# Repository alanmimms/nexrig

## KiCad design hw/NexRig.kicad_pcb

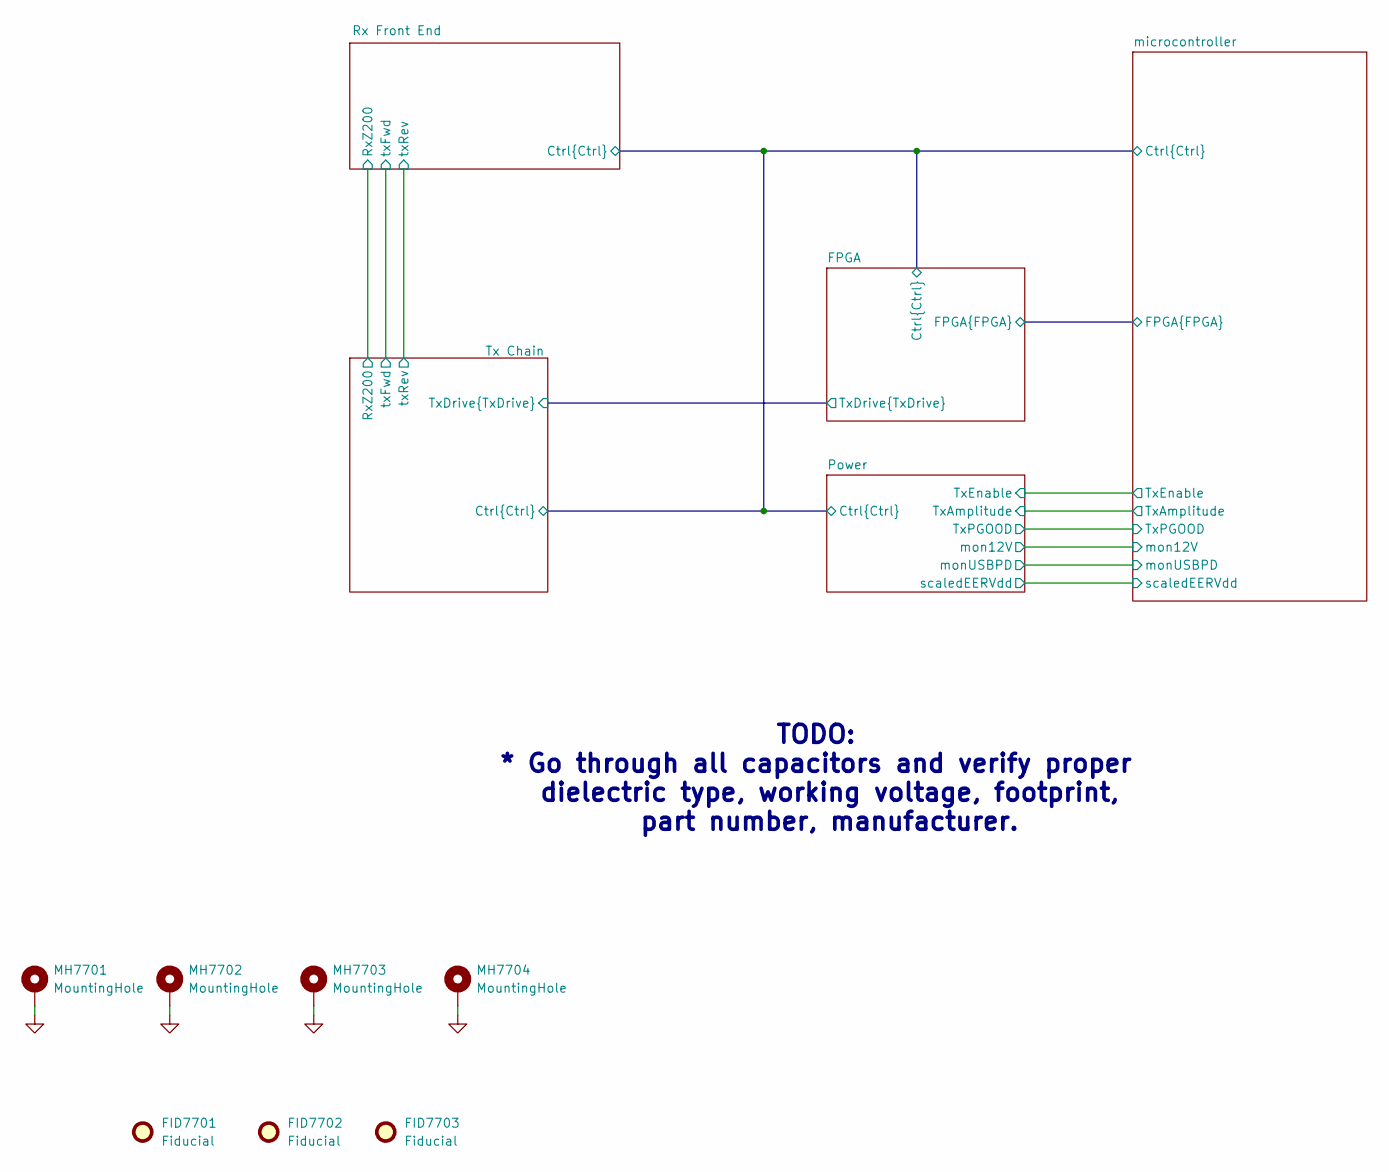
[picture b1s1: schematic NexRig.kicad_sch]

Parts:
FID7701, FID7702, FID7703: Fiducial; Fiducial_0.5mm_Mask2mm
MH7701, MH7702, MH7703, MH7704: MountingHole; MountingHole_3.2mm_M3_ISO7380_Pad

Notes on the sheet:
TODO: * Go through all capacitors and verify proper dielectric type, working voltage, footprint, part number, manufacturer.

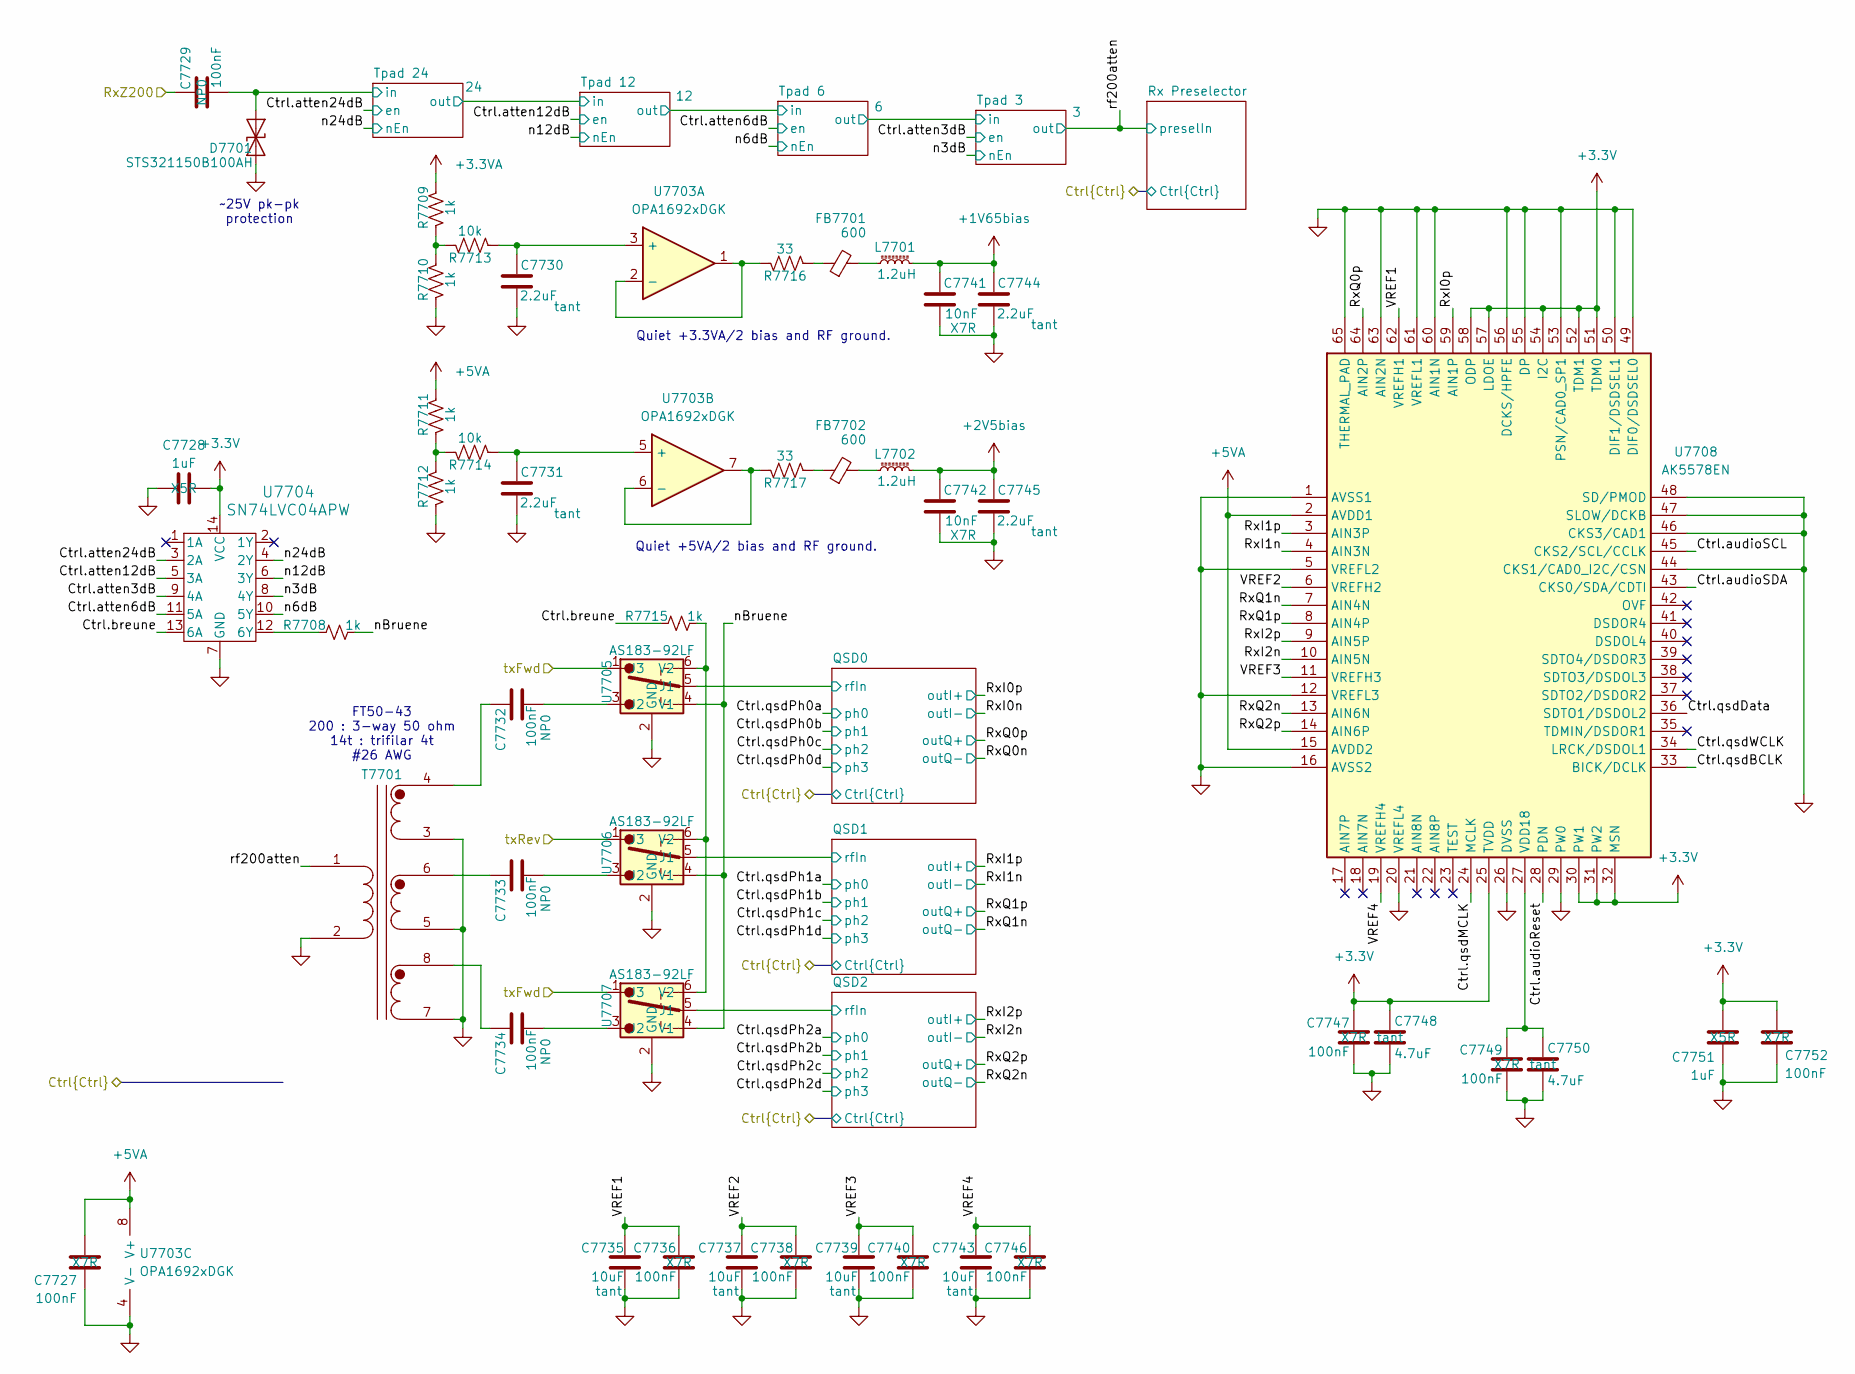
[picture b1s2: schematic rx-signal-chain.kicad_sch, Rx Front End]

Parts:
C7727, C7736, C7738, C7740, C7746, C7747, C7749, C7752: 100nF; C_0603_1608Metric; Manufacturer_Part_Number C0805F104K1RACAUTO; Mouser Part Number 80-C0805F104K1RAUTO
C7728, C7751: 1uF; C_0402_1005Metric; Manufacturer_Part_Number GRM155R61E105KE11D; Mouser Part Number 81-GRM155R61E105KE1D
C7729, C7732, C7733, C7734: 100nF; C_1206_3216Metric; Manufacturer_Part_Number GRM31C5C2A104JA01L; Mouser Part Number 81-GRM31C5C2A104JA1L
C7730, C7731, C7744, C7745: 2.2uF; C_0805_2012Metric; MfgPart T55B225M050C0200; Mouser Part Number 74-TMCP1D225MTR2F
C7735, C7737, C7739, C7743: 10uF; C_0805_2012Metric; MfgPart TMCP0J106KTR2F; Mouser Part Number 581-TAJD106K050R
C7741, C7742: 10nF; C_0603_1608Metric; Part Number GCM1885C2A103JE02J; Mouser Part Number 81-GCM1885C2A103JE2J
C7748, C7750: 4.7uF; C_0805_2012Metric; Manufacturer_Part_Number 298D475X9010M2T; Mouser Part Number 74-298D475X9010M2T
D7701: STS321150B100AH; Infineon_SG-WLL-2-3_0.58x0.28_P0.36mm
FB7701, FB7702: 600; L_0603_1608Metric; MfgPN BLM18AG601SN1D
L7701, L7702: 1.2uH; L_0805_2012Metric; Part Number CWF2012A-1R2K
R7708, R7715: 1k; R_0402_1005Metric
R7709, R7710, R7711, R7712: 1k; R_0603_1608Metric
R7713, R7714: 10k; R_0402_1005Metric
R7716, R7717: 33; R_0603_1608Metric
T7701: 12t primary : 6T #26 trifilar secondary FT37-43; Toroid-1pri-3sec-ft50
U7703: OPA1692xDGK; VSSOP-8_3x3mm_P0.65mm
U7704: SN74LVC04APW; PW14
U7705, U7706, U7707: AS183-92LF; SOT65P220X110-6N; Mouser Part Number 873-AS183-92LF
U7708: AK5578EN; QFN50P900X900X100-65N; Mouser Part Number 412-AK5578EN

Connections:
+1V65bias: C7741.1, C7744.1, L7701.2; also elsewhere on the board
+2V5bias: C7742.1, C7745.1, L7702.2; also elsewhere on the board
+3.3V: C7728.2, C7747.2, C7748.2, C7751.1, C7752.1, U7704.14 (VCC), U7708.25 (TVDD), U7708.30 (PW1), U7708.31 (PW2), U7708.32 (MSN), U7708.51 (TDM0), U7708.52 (TDM1), U7708.54 (I2C), U7708.57 (LDOE), U7708.58 (ODP); also elsewhere on the board
+3.3VA: R7709.2; also elsewhere on the board
+5VA: C7727.1, R7711.2, U7703.8 (V+), U7708.2 (AVDD1), U7708.15 (AVDD2); also elsewhere on the board
/FPGA/Ctrl.audioReset: U7708.28 (PDN); also elsewhere on the board
/FPGA/Ctrl.audioSCL: U7708.45 (CKS2/SCL/CCLK); also elsewhere on the board
/FPGA/Ctrl.audioSDA: U7708.43 (CKS0/SDA/CDTI); also elsewhere on the board
/FPGA/Ctrl.qsdBCLK: U7708.33 (BICK/DCLK); also elsewhere on the board
/FPGA/Ctrl.qsdData: U7708.36 (SDTO1/DSDOL2); also elsewhere on the board
/FPGA/Ctrl.qsdMCLK: U7708.24 (MCLK)
/FPGA/Ctrl.qsdWCLK: U7708.34 (LRCK/DSDOL1); also elsewhere on the board
/Rx Front End/Ctrl.atten3dB: U7704.9 (4A); also elsewhere on the board
/Rx Front End/Ctrl.atten6dB: U7704.11 (5A); also elsewhere on the board
/Rx Front End/Ctrl.atten12dB: U7704.5 (3A); also elsewhere on the board
/Rx Front End/Ctrl.atten24dB: U7704.3 (2A); also elsewhere on the board
/Rx Front End/Ctrl.breune: R7715.1, U7704.13 (6A)
/Rx Front End/QSD0/rfIn: U7705.5 (J1); also elsewhere on the board
/Rx Front End/QSD1/rfIn: U7706.5 (J1); also elsewhere on the board
/Rx Front End/QSD2/rfIn: U7707.5 (J1); also elsewhere on the board
/Rx Front End/RxI0p: U7708.59 (AIN1P); also elsewhere on the board
/Rx Front End/RxI1n: U7708.4 (AIN3N); also elsewhere on the board
/Rx Front End/RxI1p: U7708.3 (AIN3P); also elsewhere on the board
/Rx Front End/RxI2n: U7708.10 (AIN5N); also elsewhere on the board
/Rx Front End/RxI2p: U7708.9 (AIN5P); also elsewhere on the board
/Rx Front End/RxQ0p: U7708.64 (AIN2P); also elsewhere on the board
/Rx Front End/RxQ1n: U7708.7 (AIN4N); also elsewhere on the board
/Rx Front End/RxQ1p: U7708.8 (AIN4P); also elsewhere on the board
/Rx Front End/RxQ2n: U7708.13 (AIN6N); also elsewhere on the board
/Rx Front End/RxQ2p: U7708.14 (AIN6P); also elsewhere on the board
/Rx Front End/RxZ200: C7729.1; also elsewhere on the board
/Rx Front End/Tpad 24/in: C7729.2, D7701.1 (A1); also elsewhere on the board
/Rx Front End/VREF1: C7735.1, C7736.1, U7708.62 (VREFH1)
/Rx Front End/VREF2: C7737.1, C7738.1, U7708.6 (VREFH2)
/Rx Front End/VREF3: C7739.1, C7740.1, U7708.11 (VREFH3)
/Rx Front End/VREF4: C7743.1, C7746.1, U7708.19 (VREFH4)
/Rx Front End/n3dB: U7704.8 (4Y); also elsewhere on the board
/Rx Front End/n6dB: U7704.10 (5Y); also elsewhere on the board
/Rx Front End/n12dB: U7704.6 (3Y); also elsewhere on the board
/Rx Front End/n24dB: U7704.4 (2Y); also elsewhere on the board
/Rx Front End/nBruene: R7708.2, U7705.4 (V1), U7706.4 (V1), U7707.4 (V1)
/Rx Front End/rf200atten: T7701.1 (IN+); also elsewhere on the board
/Rx Front End/txFwd: U7705.1 (J3), U7707.1 (J3); also elsewhere on the board
/Rx Front End/txRev: U7706.1 (J3); also elsewhere on the board
unnamed: C7733.1, T7701.6 (OUT2A)
unnamed: C7734.1, T7701.8 (OUT2A)
unnamed: FB7701.1, R7716.1
unnamed: FB7701.2, L7701.1
unnamed: FB7702.1, R7717.1
unnamed: FB7702.2, L7702.1
unnamed: R7709.1, R7710.2, R7713.2
unnamed: R7711.1, R7712.2, R7714.2
unnamed: C7732.1, T7701.4 (OUT1A)
unnamed: C7730.1, R7713.1, U7703.3 (+)
unnamed: R7716.2, U7703.1, U7703.2 (-)
unnamed: C7731.1, R7714.1, U7703.5 (+)
unnamed: R7717.2, U7703.6 (-), U7703.7
unnamed: R7708.1, U7704.12 (6Y)
unnamed: C7732.2, U7705.3 (J2)
unnamed: R7715.2, U7705.6 (V2), U7706.6 (V2), U7707.6 (V2)
unnamed: C7733.2, U7706.3 (J2)
unnamed: C7734.2, U7707.3 (J2)
unnamed: C7749.2, C7750.2, U7708.27 (VDD18)

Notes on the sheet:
~25V pk-pk protection
Quiet +3.3VA/2 bias and RF ground.
FT50-43 200 : 3-way 50 ohm 14t : trifilar 4t #26 AWG
Quiet +5VA/2 bias and RF ground.

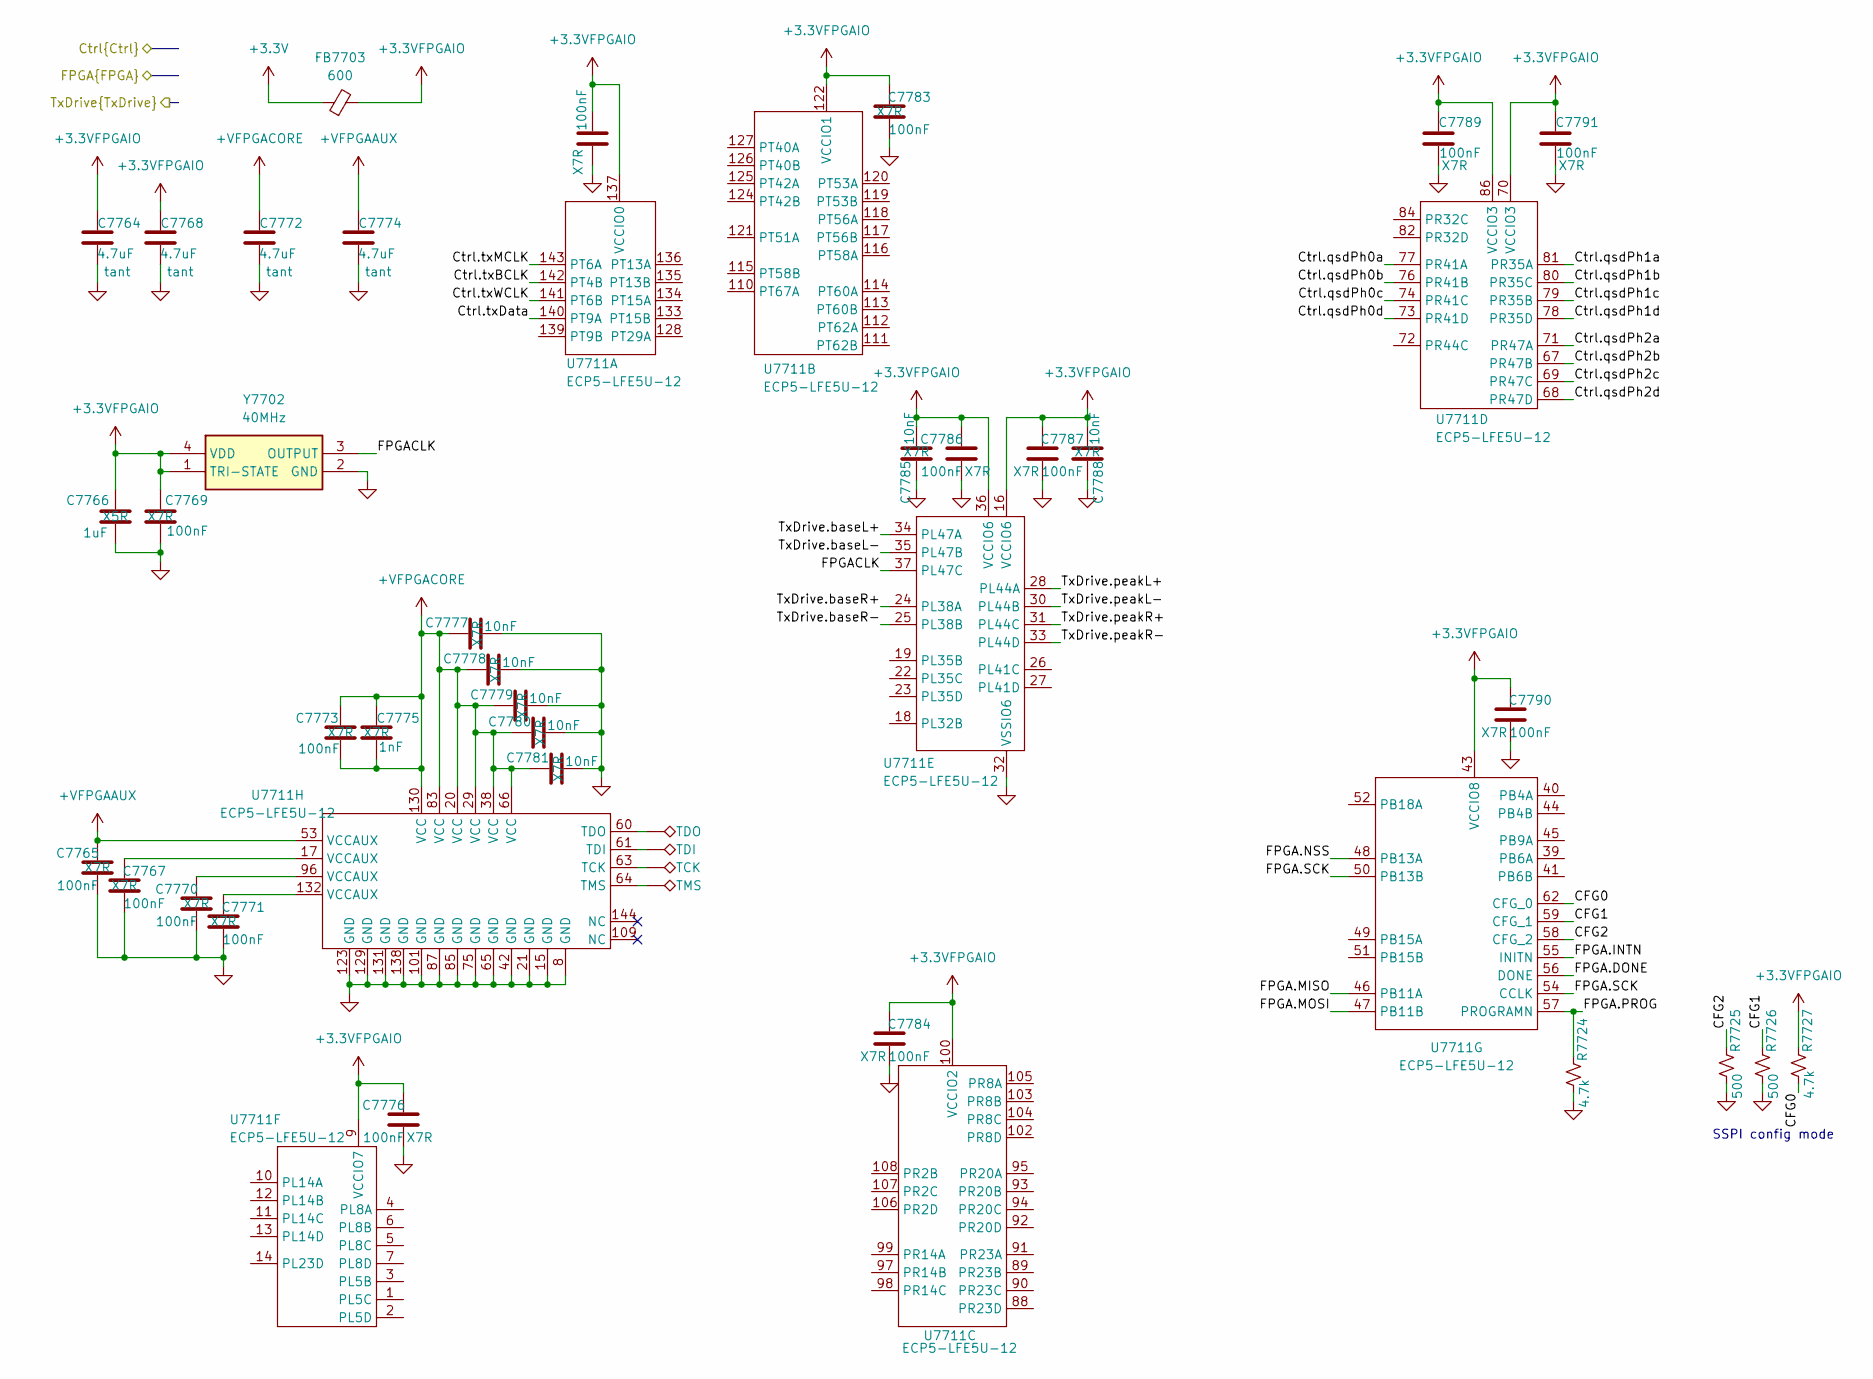
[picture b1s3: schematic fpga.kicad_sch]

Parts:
C7764, C7768, C7772, C7774: 4.7uF; C_0805_2012Metric; Manufacturer_Part_Number 298D475X9010M2T; Mouser Part Number 74-298D475X9010M2T
C7765, C7767, C7769, C7770, C7771, C7773, C7776, C7782, C7783, C7784, C7786, C7787, C7789, C7790, C7791: 100nF; C_0603_1608Metric; Manufacturer_Part_Number C0805F104K1RACAUTO; Mouser Part Number 80-C0805F104K1RAUTO
C7766: 1uF; C_0402_1005Metric; Manufacturer_Part_Number GRM155R61E105KE11D; Mouser Part Number 81-GRM155R61E105KE1D
C7775: 1nF; C_0603_1608Metric; Manufacturer_Part_Number KAF15AR71H102KM; Mouser Part Number 581-KAF15AR71H102KM
C7777, C7778, C7779, C7780, C7781, C7785, C7788: 10nF; C_0603_1608Metric; Manufacturer_Part_Number GCM1885C2A103JE02J; Mouser Part Number 81-GCM1885C2A103JE2J
FB7703: 600; L_0603_1608Metric
PG7709: TDO; TestPoint_Pad_1.0x1.0mm
PG7710: TDI; TestPoint_Pad_1.0x1.0mm
PG7711: TCK; TestPoint_Pad_1.0x1.0mm
PG7712: TMS; TestPoint_Pad_1.0x1.0mm
R7724, R7727: 4.7k; R_0603_1608Metric
R7725, R7726: 500; R_0603_1608Metric
U7711: ECP5-LFE5U-12; TQFP-144_20x20mm_P0.5mm
Y7702: 40MHz; ECSTXO201633400TR; Mouser Part Number 520-TXO-2016-33-400T

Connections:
+3.3V: FB7703.1; also elsewhere on the board
+3.3VFPGAIO: C7764.1, C7766.1, C7768.1, C7769.1, C7776.1, C7782.1, C7783.1, C7784.1, C7785.1, C7786.1, C7787.1, C7788.1, C7789.1, C7790.1, C7791.1, FB7703.2, R7727.1, U7711.9 (VCCIO7), U7711.16 (VCCIO6), U7711.36 (VCCIO6), U7711.43 (VCCIO8), U7711.70 (VCCIO3), U7711.86 (VCCIO3), U7711.100 (VCCIO2), U7711.122 (VCCIO1), U7711.137 (VCCIO0), Y7702.1 (TRI-STATE), Y7702.4 (VDD)
+VFPGAAUX: C7765.1, C7774.1, U7711.53 (VCCAUX); also elsewhere on the board
+VFPGACORE: C7772.1, C7773.1, C7773.2, C7775.1, C7775.2, C7777.2, C7778.2, C7779.2, C7780.2, C7781.2, U7711.20 (VCC), U7711.29 (VCC), U7711.38 (VCC), U7711.66 (VCC), U7711.83 (VCC), U7711.130 (VCC); also elsewhere on the board
/FPGA/CFG0: R7727.2, U7711.62 (CFG_0)
/FPGA/CFG1: R7726.1, U7711.59 (CFG_1)
/FPGA/CFG2: R7725.1, U7711.58 (CFG_2)
/FPGA/Ctrl.qsdPh0a: U7711.77 (PR41A); also elsewhere on the board
/FPGA/Ctrl.qsdPh0b: U7711.76 (PR41B); also elsewhere on the board
/FPGA/Ctrl.qsdPh0c: U7711.74 (PR41C); also elsewhere on the board
/FPGA/Ctrl.qsdPh0d: U7711.73 (PR41D); also elsewhere on the board
/FPGA/Ctrl.qsdPh1a: U7711.81 (PR35A); also elsewhere on the board
/FPGA/Ctrl.qsdPh1b: U7711.80 (PR35C); also elsewhere on the board
/FPGA/Ctrl.qsdPh1c: U7711.79 (PR35B); also elsewhere on the board
/FPGA/Ctrl.qsdPh1d: U7711.78 (PR35D); also elsewhere on the board
/FPGA/Ctrl.qsdPh2a: U7711.71 (PR47A); also elsewhere on the board
/FPGA/Ctrl.qsdPh2b: U7711.67 (PR47B); also elsewhere on the board
/FPGA/Ctrl.qsdPh2c: U7711.69 (PR47C); also elsewhere on the board
/FPGA/Ctrl.qsdPh2d: U7711.68 (PR47D); also elsewhere on the board
/FPGA/Ctrl.txBCLK: U7711.142 (PT4B); also elsewhere on the board
/FPGA/Ctrl.txData: U7711.140 (PT9A); also elsewhere on the board
/FPGA/Ctrl.txMCLK: U7711.143 (PT6A); also elsewhere on the board
/FPGA/Ctrl.txWCLK: U7711.141 (PT6B); also elsewhere on the board
/FPGA/FPGA.DONE: U7711.56 (DONE); also elsewhere on the board
/FPGA/FPGA.INTN: U7711.55 (INITN); also elsewhere on the board
/FPGA/FPGA.MISO: U7711.46 (PB11A); also elsewhere on the board
/FPGA/FPGA.MOSI: U7711.47 (PB11B); also elsewhere on the board
/FPGA/FPGA.NSS: U7711.48 (PB13A); also elsewhere on the board
/FPGA/FPGA.PROG: R7724.1, U7711.57 (PROGRAMN); also elsewhere on the board
/FPGA/FPGA.SCK: U7711.50 (PB13B), U7711.54 (CCLK); also elsewhere on the board
/FPGA/FPGACLK: U7711.37 (PL47C), Y7702.3 (OUTPUT)
/FPGA/TxDrive.baseL+: U7711.34 (PL47A); also elsewhere on the board
/FPGA/TxDrive.baseL-: U7711.35 (PL47B); also elsewhere on the board
/FPGA/TxDrive.baseR+: U7711.24 (PL38A); also elsewhere on the board
/FPGA/TxDrive.baseR-: U7711.25 (PL38B); also elsewhere on the board
/FPGA/TxDrive.peakL+: U7711.28 (PL44A); also elsewhere on the board
/FPGA/TxDrive.peakL-: U7711.30 (PL44B); also elsewhere on the board
/FPGA/TxDrive.peakR+: U7711.31 (PL44C); also elsewhere on the board
/FPGA/TxDrive.peakR-: U7711.33 (PL44D); also elsewhere on the board
unnamed: C7767.1, U7711.17 (VCCAUX)
unnamed: C7770.1, U7711.96 (VCCAUX)
unnamed: C7771.1, U7711.132 (VCCAUX)
unnamed: PG7711.1, U7711.63 (TCK)
unnamed: PG7710.1, U7711.61 (TDI)
unnamed: PG7709.1, U7711.60 (TDO)
unnamed: PG7712.1, U7711.64 (TMS)

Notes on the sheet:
SSPI config mode

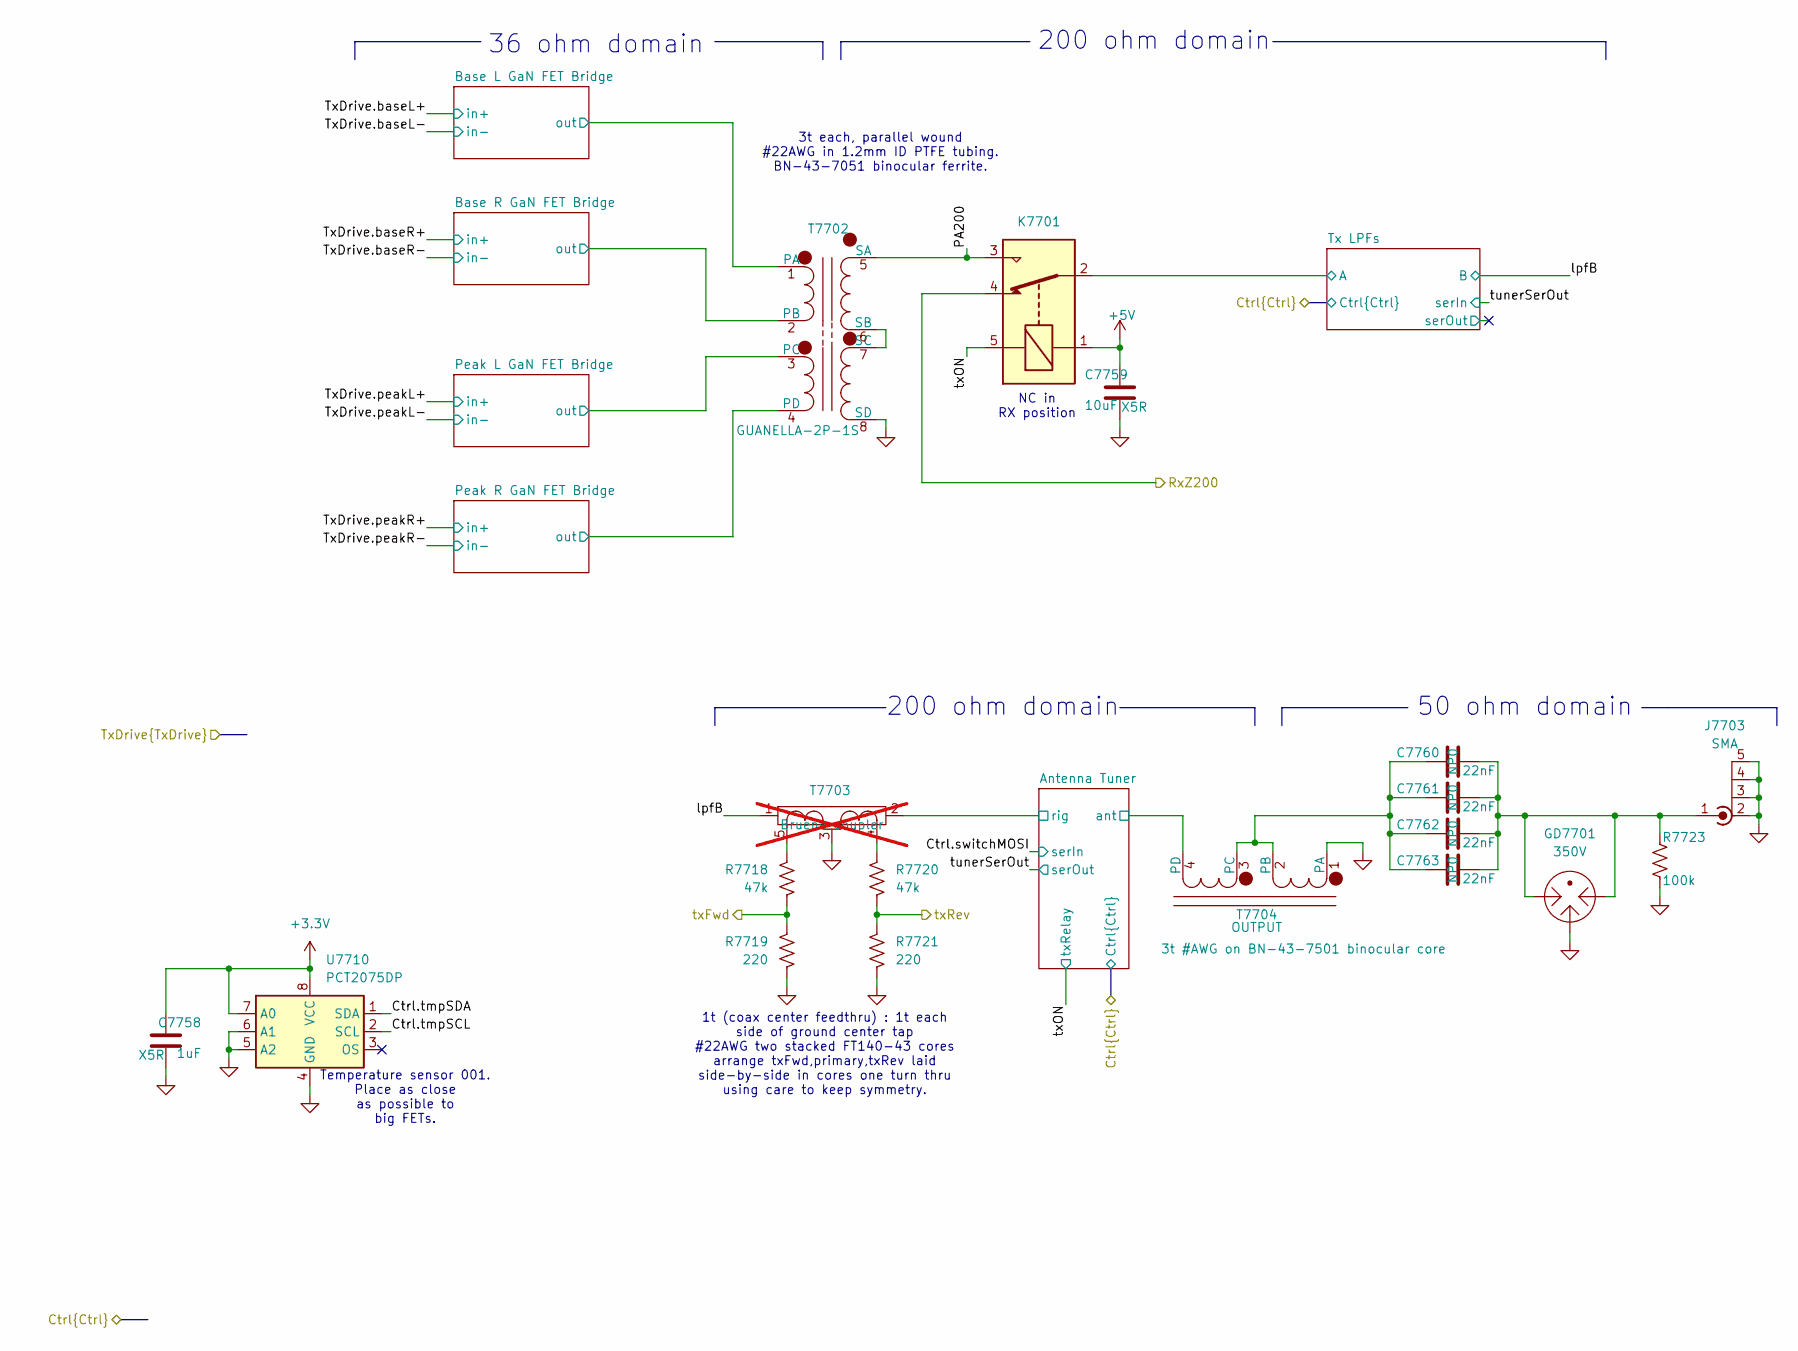
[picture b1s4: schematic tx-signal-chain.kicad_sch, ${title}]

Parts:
C7758: 1uF; C_0402_1005Metric; Manufacturer_Part_Number GRM155R61E105KE11D; Mouser Part Number 81-GRM155R61E105KE1D
C7759: 10uF; C_0603_1608Metric; Manufacturer_Part_Number 81-GXT155R71E223KE1D; Mouser Part Number 963-MLAST168BB5106MT
C7760, C7761, C7762, C7763: 22nF; C_1206_3216Metric; Manufacturer_Part_Number CC1210JKNPOCBN223; Mouser Part Number 603-CC121JKNPOCBN223
GD7701: 350V; GDT3535S1RP; Manufacturer_Part_Number GDT35-35-S1-RP; Mouser Part Number 652-GDT35-35-S1-RP
J7703: SMA; RFPCSMA27F
K7701: G5Q-14-05; Relay_SPDT_Omron-G5Q-1
R7718, R7720: 47k; R_0603_1608Metric; Manufacturer_Part_Number MCT06030C4702FP500; Mouser Part Number 594-MCT06030C4702FP5
R7719, R7721: 220; R_0603_1608Metric; Manufacturer_Part_Number MCT06030C2200FP500; Mouser Part Number 594-MCT06030C2200FP5
R7723: 100k; R_1206_3216Metric; Manufacturer_Part_Number ERJ-P08J104V; Mouser Part Number 667-ERJ-P08J104V
T7702: GUANELLA-2P-1S; Guanella-2P-2S
T7703: Bruene coupler; BN-43-7051-1P-1S-CT; not fitted
T7704: OUTPUT; Guanella-1P-1S
U7710: PCT2075DP; TSSOP-8_3x3mm_P0.65mm

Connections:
+3.3V: C7758.1, U7710.7 (A0), U7710.8 (VCC); also elsewhere on the board
/FPGA/Ctrl.tmpSCL: U7710.2 (SCL); also elsewhere on the board
/FPGA/Ctrl.tmpSDA: U7710.1 (SDA); also elsewhere on the board
/Rx Front End/txFwd: R7718.2, R7719.1; also elsewhere on the board
/Rx Front End/txRev: R7720.2, R7721.1; also elsewhere on the board
/Tx Chain/Antenna Tuner/rig: T7703.2; also elsewhere on the board
/Tx Chain/Base L GaN FET Bridge/out: T7702.1 (PA); also elsewhere on the board
/Tx Chain/Base R GaN FET Bridge/out: T7702.2 (PB); also elsewhere on the board
/Tx Chain/Peak L GaN FET Bridge/out: T7702.3 (PC); also elsewhere on the board
/Tx Chain/Peak R GaN FET Bridge/out: T7702.4 (PD); also elsewhere on the board
/Tx Chain/lpfB: T7703.1; also elsewhere on the board
/Tx Chain/txON: K7701.5; also elsewhere on the board
unnamed: C7760.2, C7761.2, C7762.2, C7763.2, GD7701.1, GD7701.3, J7703.1 (In), R7723.1
unnamed 312: K7701.4; also elsewhere on the board
unnamed: R7718.1, T7703.5
unnamed: R7720.1, T7703.4
unnamed: T7702.6 (SB), T7702.7 (SC)
unnamed: C7760.1, C7761.1, C7762.1, C7763.1, T7704.2 (PB), T7704.3 (PC)

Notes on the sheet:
50 ohm domain
1t (coax center feedthru) : 1t each side of ground center tap #22AWG two stacked FT140-43 cores arrange txFwd,primary,txRev laid side-by-side in cores one turn thru using care to keep symmetry.
3t each, parallel wound #22AWG in 1.2mm ID PTFE tubing. BN-43-7051 binocular ferrite.
36 ohm domain
200 ohm domain
NC in RX position
Temperature sensor 001. Place as close as possible to big FETs.

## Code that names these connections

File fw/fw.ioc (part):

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Mcu.Name=STM32H753ZITx
Mcu.Package=LQFP144
Mcu.UserName=STM32H753ZITx
PA1.GPIOParameters=GPIO_Label
PA1.GPIO_Label=EthCLK
PA1.Mode=RMII
PA1.Signal=ETH_REF_CLK
PA11.GPIOParameters=GPIO_PuPd,GPIO_Label
PA11.GPIO_Label=TxEnable
PA11.GPIO_PuPd=GPIO_PULLDOWN
PA11.Signal=GPIO_Output
PA13\ (JTMS/SWDIO).GPIOParameters=GPIO_Label
PA13\ (JTMS/SWDIO).GPIO_Label=SWDIO
PA13\ (JTMS/SWDIO).Mode=Serial_Wire
PA13\ (JTMS/SWDIO).Signal=DEBUG_JTMS-SWDIO
PA14\ (JTCK/SWCLK).GPIOParameters=GPIO_Label
PA14\ (JTCK/SWCLK).GPIO_Label=SWCL
PA14\ (JTCK/SWCLK).Mode=Serial_Wire
PA14\ (JTCK/SWCLK).Signal=DEBUG_JTCK-SWCLK
PA15\ (JTDI).GPIOParameters=GPIO_Speed,GPIO_PuPd,GPIO_Label
PA15\ (JTDI).GPIO_Label=FPGA_NSS
PA15\ (JTDI).GPIO_PuPd=GPIO_PULLUP
PA15\ (JTDI).GPIO_Speed=GPIO_SPEED_FREQ_MEDIUM
PA15\ (JTDI).Mode=NSS_Signal_Hard_Output
PA15\ (JTDI).Signal=SPI3_NSS
PA2.GPIOParameters=GPIO_Label
PA2.GPIO_Label=EthMDIO
PA2.Mode=RMII
PA2.Signal=ETH_MDIO
PA4.GPIOParameters=GPIO_Label
PA4.GPIO_Label=TxAmplitude
PA4.Signal=COMP_DAC11_group
PA5.GPIOParameters=GPIO_Label
PA5.GPIO_Label=Ctrl.tuneSCK
PA5.Mode=TX_Only_Simplex_Unidirect_Master
PA5.Signal=SPI6_SCK
PA6.GPIOParameters=GPIO_PuPd,GPIO_Label
PA6.GPIO_Label=Ctrl_audioReset
PA6.GPIO_PuPd=GPIO_PULLDOWN
PA6.Signal=GPIO_Output
PA7.GPIOParameters=GPIO_Label
PA7.GPIO_Label=EthCRS_DV
PA7.Mode=RMII
PA7.Signal=ETH_CRS_DV
PA8.Signal=GPIO_Analog
PA9.GPIOParameters=GPIO_Label
PA9.GPIO_Label=monUSBPD
PA9.Signal=GPIO_Analog
PB10.GPIOParameters=GPIO_Speed,GPIO_Label
PB10.GPIO_Label=Ctrl_switchSCK
PB10.GPIO_Speed=GPIO_SPEED_FREQ_HIGH
PB10.Mode=TX_Only_Simplex_Unidirect_Master
PB10.Signal=SPI2_SCK
PB11.GPIOParameters=GPIO_Label
PB11.GPIO_Label=EthTxEnable
PB11.Mode=RMII
PB11.Signal=ETH_TX_EN
PB12.GPIOParameters=GPIO_Label
PB12.GPIO_Label=EthTXD0
PB12.Mode=RMII
PB12.Signal=ETH_TXD0
PB13.GPIOParameters=GPIO_Label
PB13.GPIO_Label=EthTXD1
PB13.Mode=RMII
PB13.Signal=ETH_TXD1
PB2.GPIOParameters=GPIO_Label
PB2.GPIO_Label=Ctrl.qsdData
PB2.Mode=SAI_A_AsyncSlave
PB2.Signal=SAI1_SD_A
PB3\ (JTDO/TRACESWO).Signal=DEBUG_JTDO-SWO
PB6.GPIOParameters=GPIO_Speed,GPIO_Label,GPIO_Pu
PB6.GPIO_Label=Ctrl_tmpSCL
PB6.GPIO_Pu=GPIO_PULLUP
PB6.GPIO_Speed=GPIO_SPEED_FREQ_MEDIUM
PB6.Mode=I2C
PB6.Signal=I2C1_SCL
PB7.GPIOParameters=GPIO_Speed,GPIO_Label,GPIO_Pu
PB7.GPIO_Label=Ctrl_tmpSDA
PB7.GPIO_Pu=GPIO_PULLUP
PB7.GPIO_Speed=GPIO_SPEED_FREQ_MEDIUM
PB7.Mode=I2C
PB7.Signal=I2C1_SDA
PC0.GPIOParameters=GPIO_Label
PC0.GPIO_Label=Ctrl_enable5V
PC0.Signal=GPIO_Output
PC1.GPIOParameters=GPIO_Label
PC1.GPIO_Label=EthMDC
PC1.Mode=RMII
PC1.Signal=ETH_MDC
PC10.GPIOParameters=GPIO_Speed,GPIO_Label
PC10.GPIO_Label=FPGA_SCK
PC10.GPIO_Speed=GPIO_SPEED_FREQ_HIGH
PC10.Mode=Full_Duplex_Master
PC10.Signal=SPI3_SCK
PC11.GPIOParameters=GPIO_PuPd,GPIO_Label
PC11.GPIO_Label=FPGA_MISO
PC11.GPIO_PuPd=GPIO_PULLUP
PC11.Mode=Full_Duplex_Master
PC11.Signal=SPI3_MISO
PC12.GPIOParameters=GPIO_Label,GPIO_Speed
PC12.GPIO_Label=FPGA_MOSI
PC12.GPIO_Speed=GPIO_SPEED_FREQ_HIGH
PC12.Mode=Full_Duplex_Master
PC12.Signal=SPI3_MOSI
PC3_C.GPIOParameters=GPIO_Speed,GPIO_Label
PC3_C.GPIO_Label=Ctrl_switchMOSI
PC3_C.GPIO_Speed=GPIO_SPEED_FREQ_HIGH
PC3_C.Mode=TX_Only_Simplex_Unidirect_Master
PC3_C.Signal=SPI2_MOSI
PC4.GPIOParameters=GPIO_Label
PC4.GPIO_Label=EthRXD0
PC4.Mode=RMII
PC4.Signal=ETH_RXD0
PC5.GPIOParameters=GPIO_Label
PC5.GPIO_Label=EthRXD1
PC5.Mode=RMII
PC5.Signal=ETH_RXD1
PC6.GPIOParameters=GPIO_PuPd,GPIO_Label
PC6.GPIO_Label=TxPGOOD
PC6.GPIO_PuPd=GPIO_PULLDOWN
PC6.Signal=GPIO_Input
PC8.GPIOParameters=GPIO_Label
PC8.GPIO_Label=Ctrl_bruene
PC8.Signal=GPIO_Output
PD12.GPIOParameters=GPIO_Speed,GPIO_Label,GPIO_Pu
PD12.GPIO_Label=Ctrl_audioSCL
PD12.GPIO_Pu=GPIO_NOPULL
PD12.GPIO_Speed=GPIO_SPEED_FREQ_MEDIUM
PD12.Mode=I2C
PD12.Signal=I2C4_SCL
PD7.GPIOParameters=GPIO_Speed,GPIO_Label
PD7.GPIO_Label=dispMOSI
PD7.GPIO_Speed=GPIO_SPEED_FREQ_HIGH
PD7.Mode=TX_Only_Simplex_Unidirect_Master
PD7.Signal=SPI1_MOSI
PE0.GPIOParameters=GPIO_PuPd,GPIO_Label
PE0.GPIO_Label=CDONE
PE0.GPIO_PuPd=GPIO_PULLDOWN
PE0.Signal=GPIO_Input
PE10.GPIOParameters=GPIO_Label
PE10.GPIO_Label=Ctrl_atten3dB
PE10.Signal=GPIO_Output
PE11.GPIOParameters=GPIO_PuPd,GPIO_Label
PE11.GPIO_Label=Ctrl.qsdNSS
PE11.GPIO_PuPd=GPIO_PULLUP
PE11.Mode=NSS_Signal_Hard_Output
PE11.Signal=SPI4_NSS
PE12.GPIOParameters=GPIO_PuPd,GPIO_Label
PE12.GPIO_Label=dispRESET
PE12.GPIO_PuPd=GPIO_PULLDOWN
PE12.Signal=GPIO_Output
PE13.GPIOParameters=GPIO_Label
PE13.GPIO_Label=dispDC
PE13.Signal=GPIO_Output
PE15.GPIOParameters=GPIO_PuPd,GPIO_Label
PE15.GPIO_Label=FPGA.RESET
PE15.GPIO_PuPd=GPIO_PULLDOWN
PE15.Signal=GPIO_Output
PE2.GPIOParameters=GPIO_Speed,GPIO_Label
PE2.GPIO_Label=Ctrl.qsdSCK
PE2.GPIO_Speed=GPIO_SPEED_FREQ_HIGH
PE2.Mode=TX_Only_Simplex_Unidirect_Master
PE2.Signal=SPI4_SCK
PE3.GPIOParameters=GPIO_Label
PE3.GPIO_Label=Ctrl.txData
PE3.Mode=SAI_B_MasterWithClock
PE3.Signal=SAI1_SD_B
PE4.GPIOParameters=GPIO_Label
PE4.GPIO_Label=Ctrl.qsdWCLK
PE4.Mode=SAI_A_AsyncSlave
PE4.Signal=SAI1_FS_A
PE5.GPIOParameters=GPIO_Label
PE5.GPIO_Label=Ctrl.qsdBCLK
PE5.Mode=SAI_A_AsyncSlave
PE5.Signal=SAI1_SCK_A
PE6.GPIOParameters=GPIO_Label
PE6.GPIO_Label=Ctrl.qsdMOSI
PE6.Mode=TX_Only_Simplex_Unidirect_Master
PE6.Signal=SPI4_MOSI
PE7.GPIOParameters=GPIO_Label
PE7.GPIO_Label=Ctrl_atten24dB
PE7.Signal=GPIO_Output
PE8.GPIOParameters=GPIO_Label
PE8.GPIO_Label=Ctrl_atten12dB
PE8.Signal=GPIO_Output
PE9.GPIOParameters=GPIO_Label
PE9.GPIO_Label=Ctrl_atten6dB
PE9.Signal=GPIO_Output
PF0.Signal=GPIO_Output
PF1.GPIOParameters=GPIO_Label
PF1.GPIO_Label=Ctrl.enable3V3
PF1.Signal=GPIO_Output
PF10.GPIOParameters=GPIO_Label
PF10.GPIO_Label=Ctrl_usbPOK2
PF10.Signal=GPIO_Input
PF11.GPIOParameters=GPIO_Label
PF11.GPIO_Label=Ctrl.usbPOK3
PF11.Signal=GPIO_Input
PF12.GPIOParameters=GPIO_Label
PF12.GPIO_Label=scaledEERVdd
PF12.Mode=IN6-Single-Ended
PF12.Signal=ADC1_INP6
PF13.GPIOParameters=GPIO_Label
PF13.GPIO_Label=Ctrl.switchRCK
PF13.Signal=GPIO_Output
PF14.Signal=GPIO_Input
PF15.GPIOParameters=GPIO_Speed,GPIO_Label,GPIO_Pu
PF15.GPIO_Label=Ctrl_audioSDA
PF15.GPIO_Pu=GPIO_NOPULL
PF15.GPIO_Speed=GPIO_SPEED_FREQ_MEDIUM
PF15.Mode=I2C
PF15.Signal=I2C4_SDA
PF2.GPIOParameters=GPIO_Label
PF2.GPIO_Label=Ctrl.enable5V
PF2.Signal=GPIO_Output
PF3.GPIOParameters=GPIO_Label
PF3.GPIO_Label=Ctrl.enable3VA
PF3.Signal=GPIO_Output
PF4.GPIOParameters=GPIO_Label
PF4.GPIO_Label=Ctrl.enable5VA
PF4.Signal=GPIO_Output
PF5.GPIOParameters=GPIO_Label
PF5.GPIO_Label=Ctrl.enableFPGA1V2
PF5.Signal=GPIO_Output
PF6.GPIOParameters=GPIO_Label
PF6.GPIO_Label=Ctrl.enableFPGAIO
PF6.Signal=GPIO_Output
PF7.GPIOParameters=GPIO_Label
PF7.GPIO_Label=Ctrl.txMCLK
PF7.Mode=SAI_B_MasterWithClock
PF7.Signal=SAI1_MCLK_B
PF8.GPIOParameters=GPIO_Label
PF8.GPIO_Label=Ctrl.txBCLK
PF8.Mode=SAI_B_MasterWithClock
PF8.Signal=SAI1_SCK_B
PF9.GPIOParameters=GPIO_Label
PF9.GPIO_Label=Ctrl.txWCLK
PF9.Mode=SAI_B_MasterWithClock
PF9.Signal=SAI1_FS_B
PG10.GPIOParameters=GPIO_Speed,GPIO_PuPd,GPIO_Label
PG10.GPIO_Label=dispNSS
PG10.GPIO_PuPd=GPIO_PULLUP
PG10.GPIO_Speed=GPIO_SPEED_FREQ_MEDIUM
PG10.Mode=NSS_Signal_Hard_Output
PG10.Signal=SPI1_NSS
PG11.GPIOParameters=GPIO_Speed,GPIO_Label
PG11.GPIO_Label=dispSCK
PG11.GPIO_Speed=GPIO_SPEED_FREQ_HIGH
PG11.Mode=TX_Only_Simplex_Unidirect_Master
PG11.Signal=SPI1_SCK
PG14.GPIOParameters=GPIO_Label
PG14.GPIO_Label=Ctrl.tuneMOSI
PG14.Mode=TX_Only_Simplex_Unidirect_Master
PG14.Signal=SPI6_MOSI
PG15.GPIOParameters=GPIO_Label
PG15.GPIO_Label=Ctrl.tuneRCK
PG15.Signal=GPIO_Output
PG8.GPIOParameters=GPIO_Label
PG8.GPIO_Label=Ctrl.tuneNSS
PG8.Mode=NSS_Signal_Hard_Output
PG8.Signal=SPI6_NSS
PH0-OSC_IN\ (PH0).GPIOParameters=GPIO_Label
PH0-OSC_IN\ (PH0).GPIO_Label=STM32clock
PH0-OSC_IN\ (PH0).Mode=HSE-External-Clock-Source
PH0-OSC_IN\ (PH0).Signal=RCC_OSC_IN
RCC.SYSCLKFreq_VALUE=64000000
board=custom

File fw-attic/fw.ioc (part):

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Mcu.Name=STM32H753ZITx
Mcu.Package=LQFP144
Mcu.UserName=STM32H753ZITx
PA11.Mode=Device_Only
PA11.Signal=USB_OTG_FS_DM
PA12.Mode=Device_Only
PA12.Signal=USB_OTG_FS_DP
PA15\ (JTDI).GPIOParameters=GPIO_Label
PA15\ (JTDI).GPIO_Label=TxNSS
PA15\ (JTDI).Mode=NSS_Signal_Hard_Output
PA15\ (JTDI).Signal=SPI3_NSS
PA3.Mode=Device_HS
PA3.Signal=USB_OTG_HS_ULPI_D0
PA5.Mode=Device_HS
PA5.Signal=USB_OTG_HS_ULPI_CK
PA6.GPIOParameters=GPIO_Label
PA6.GPIO_Label=RxQ
PA6.Signal=ADCx_INP3
PA7.GPIOParameters=GPIO_Label
PA7.GPIO_Label=RxMOSI
PA7.Mode=Full_Duplex_Master
PA7.Signal=SPI1_MOSI
PA8.GPIOParameters=GPIO_Label
PA8.GPIO_Label=VFOSCL
PA8.Mode=I2C
PA8.Signal=I2C3_SCL
PA9.Mode=Activate_VBUS
PA9.Signal=USB_OTG_FS_VBUS
PB1.Mode=Device_HS
PB1.Signal=USB_OTG_HS_ULPI_D2
PB10.Mode=Device_HS
PB10.Signal=USB_OTG_HS_ULPI_D3
PB11.Mode=Device_HS
PB11.Signal=USB_OTG_HS_ULPI_D4
PB12.Mode=Device_HS
PB12.Signal=USB_OTG_HS_ULPI_D5
PB13.Mode=Device_HS
PB13.Signal=USB_OTG_HS_ULPI_D6
PB2.GPIOParameters=GPIO_Label
PB2.GPIO_Label=TxMOSI
PB2.Mode=Full_Duplex_Master
PB2.Signal=SPI3_MOSI
PB5.Mode=Device_HS
PB5.Signal=USB_OTG_HS_ULPI_D7
PB6.GPIOParameters=GPIO_Label
PB6.GPIO_Label=DbgUARTTX
PB6.Mode=Asynchronous
PB6.Signal=LPUART1_TX
PB7.GPIOParameters=GPIO_Label,GPIO_PuPd
PB7.GPIO_Label=DbgUARTRX
PB7.GPIO_PuPd=GPIO_PULLUP
PB7.Mode=Asynchronous
PB7.Signal=LPUART1_RX
PC0.Mode=Device_HS
PC0.Signal=USB_OTG_HS_ULPI_STP
PC10.GPIOParameters=GPIO_Label
PC10.GPIO_Label=TxSCK
PC10.Mode=Full_Duplex_Master
PC10.Signal=SPI3_SCK
PC11.GPIOParameters=GPIO_Label
PC11.GPIO_Label=TxMISO
PC11.Mode=Full_Duplex_Master
PC11.Signal=SPI3_MISO
PC14-OSC32_IN\ (OSC32_IN).Signal=RCC_OSC32_IN
PC15-OSC32_OUT\ (OSC32_OUT).Signal=RCC_OSC32_OUT
PC2_C.Mode=Device_HS
PC2_C.Signal=USB_OTG_HS_ULPI_DIR
PC3_C.Mode=Device_HS
PC3_C.Signal=USB_OTG_HS_ULPI_NXT
PC9.GPIOParameters=GPIO_Label
PC9.GPIO_Label=VFOSDA
PC9.Mode=I2C
PC9.Signal=I2C3_SDA
PD0.GPIOParameters=GPIO_Label
PD0.GPIO_Label=TxTuneLDAC-
PD0.Signal=GPIO_Output
PE1.GPIOParameters=GPIO_Label
PE1.GPIO_Label=YellowLED
PE1.Signal=GPIO_Output
PE2.GPIOParameters=GPIO_Label
PE2.GPIO_Label=TxIQSCK
PE2.Mode=Full_Duplex_Master
PE2.Signal=SPI4_SCK
PE4.GPIOParameters=GPIO_Label
PE4.GPIO_Label=TxIQNSS
PE4.Mode=NSS_Signal_Hard_Output
PE4.Signal=SPI4_NSS
PE5.GPIOParameters=GPIO_Label
PE5.GPIO_Label=TxIQMISO
PE5.Mode=Full_Duplex_Master
PE5.Signal=SPI4_MISO
PE6.GPIOParameters=GPIO_Label
PE6.GPIO_Label=TxIQMOSI
PE6.Mode=Full_Duplex_Master
PE6.Signal=SPI4_MOSI
PF0.GPIOParameters=GPIO_PuPd,GPIO_Label
PF0.GPIO_Label=USBFault-
PF0.GPIO_PuPd=GPIO_PULLUP
PF0.Signal=GPIO_Input
PF11.GPIOParameters=GPIO_Label
PF11.GPIO_Label=RxI
PF11.Mode=IN2-Single-Ended
PF11.Signal=ADC1_INP2
PF13.GPIOParameters=GPIO_Label
PF13.GPIO_Label=AntVSWR
PF13.Mode=IN2-Single-Ended
PF13.Signal=ADC2_INP2
PF2.GPIOParameters=GPIO_Label
PF2.GPIO_Label=TxEnable
PF2.Signal=GPIO_Output
PG0.GPIOParameters=GPIO_Label
PG0.GPIO_Label=RxTuneLDAC-
PG0.Signal=GPIO_Input
PG1.GPIOParameters=GPIO_Label
PG1.GPIO_Label=TxIQLDAC-
PG1.Signal=GPIO_Input
PG10.GPIOParameters=GPIO_Label
PG10.GPIO_Label=RxNSS
PG10.Mode=NSS_Signal_Hard_Output
PG10.Signal=SPI1_NSS
PG11.GPIOParameters=GPIO_Label
PG11.GPIO_Label=RxSCK
PG11.Mode=Full_Duplex_Master
PG11.Signal=SPI1_SCK
PG2.GPIOParameters=GPIO_Label
PG2.GPIO_Label=RFGainHiLo
PG2.Signal=GPIO_Output
PG9.GPIOParameters=GPIO_Label
PG9.GPIO_Label=RxMISO
PG9.Mode=Full_Duplex_Master
PG9.Signal=SPI1_MISO
PH0-OSC_IN\ (PH0).Signal=RCC_OSC_IN
PH1-OSC_OUT\ (PH1).Signal=RCC_OSC_OUT
RCC.HSE_VALUE=8000000
RCC.SYSCLKFreq_VALUE=64000000
board=NUCLEO-H753ZI
boardIOC=true
